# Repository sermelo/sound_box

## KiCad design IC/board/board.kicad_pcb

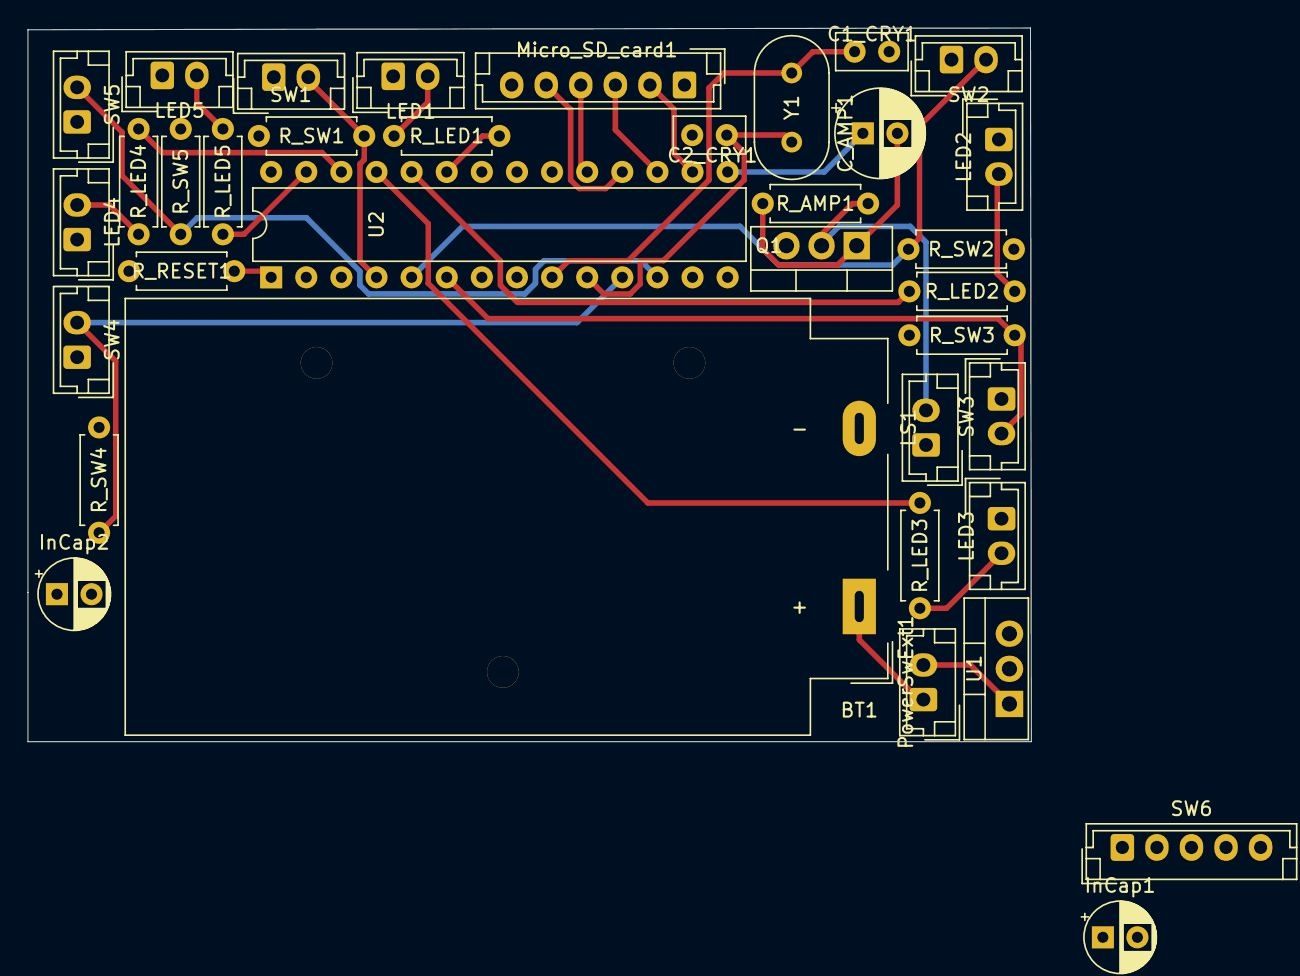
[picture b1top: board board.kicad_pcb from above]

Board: 4 copper layers, 72.6 x 51.6 mm, 36 parts (0 on the bottom side), 28 nets.

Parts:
BT1: 9V; BatteryHolder_MPD_BA9VPC_1xPP3
C1_CRY1, C2_CRY1: 22pF; C_Disc_D5.0mm_W2.5mm_P2.50mm
C_AMP1: 100uF; CP_Radial_D6.3mm_P2.50mm
InCap1: 0.33uF; CP_Radial_D5.0mm_P2.50mm
InCap2: 0.1uF; CP_Radial_D5.0mm_P2.50mm
LED1, LED2, LED3, LED4, LED5: LED; JST_EH_B2B-EH-A_1x02_P2.50mm_Vertical
LS1: Speaker; JST_EH_B2B-EH-A_1x02_P2.50mm_Vertical
Micro_SD_card1: Conn_01x06_Female; JST_EH_B6B-EH-A_1x06_P2.50mm_Vertical
PowerSwExt1: SW_DPST_x2; JST_EH_B2B-EH-A_1x02_P2.50mm_Vertical
Q1: IRLZ44N; TO-220-3_Vertical
R_AMP1: 10K; R_Axial_DIN0207_L6.3mm_D2.5mm_P7.62mm_Horizontal
R_LED1, R_LED2, R_LED3, R_LED4, R_LED5: 290; R_Axial_DIN0207_L6.3mm_D2.5mm_P7.62mm_Horizontal
R_RESET1: 10K; R_Axial_DIN0207_L6.3mm_D2.5mm_P7.62mm_Horizontal
R_SW1, R_SW2, R_SW3, R_SW4, R_SW5: 10K; R_Axial_DIN0207_L6.3mm_D2.5mm_P7.62mm_Horizontal
SW1, SW2, SW3, SW4, SW5: SW_Push; JST_EH_B2B-EH-A_1x02_P2.50mm_Vertical
SW6: Rotary_Encoder_Switch; JST_EH_B5B-EH-A_1x05_P2.50mm_Vertical
U1: L7805; TO-220-3_Vertical
U2: ATmega328P-PU; DIP-28_W7.62mm
Y1: 16Mhz; Resonator-2Pin_W10.0mm_H5.0mm

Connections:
unnamed: BT1.1, InCap1.1, PowerSwExt1.1
unnamed: BT1.2, C1_CRY1.2, C2_CRY1.2, InCap1.2, InCap2.2, LED1.1, LED2.1, LED3.1, LED4.1, LED5.1, Micro_SD_card1.6, Q1.3, SW1.1, SW2.1, SW3.1, SW4.1, SW5.1, U1.2, U2.8, U2.22
unnamed: C1_CRY1.1, U2.9, Y1.1
unnamed: C2_CRY1.1, U2.10, Y1.2
unnamed: C_AMP1.1, U2.15
unnamed: C_AMP1.2, Q1.1, R_AMP1.1
unnamed: InCap2.1, LS1.1, Micro_SD_card1.1, R_RESET1.2, R_SW1.1, R_SW2.1, R_SW3.1, R_SW4.1, R_SW5.1, U1.3, U2.7, U2.20
unnamed: LED1.2, R_LED1.1
unnamed: LED2.2, R_LED2.1
unnamed: LED3.2, R_LED3.1
unnamed: LED4.2, R_LED4.1
unnamed: LED5.2, R_LED5.1
unnamed: LS1.2, Q1.2, R_AMP1.2
unnamed: Micro_SD_card1.2, U2.16
unnamed: Micro_SD_card1.3, U2.17
unnamed: Micro_SD_card1.4, U2.19
unnamed: Micro_SD_card1.5, U2.18
unnamed: R_LED1.2, U2.23
unnamed: R_LED2.2, U2.24
unnamed: R_LED3.2, U2.25
unnamed: R_LED4.2, U2.26
unnamed: R_LED5.2, U2.27
unnamed: R_RESET1.1, U2.1
unnamed: R_SW1.2, SW1.2, U2.4
unnamed: R_SW2.2, SW2.2, U2.5
unnamed: R_SW3.2, SW3.2, U2.6
unnamed: R_SW4.2, SW4.2, U2.11
unnamed: R_SW5.2, SW5.2, U2.12

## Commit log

2022-03-02 Add current version
2022-03-07 Update the Cad and and new code
2022-03-11 Add gitignore file
2022-03-11 Clean cad files
2022-03-11 Add IC designs
2022-06-08 Update to las kicad version
2022-06-08 Add PAM amplifier
2022-06-08 Remove LED resistors. With new buttons they are not needed
2022-06-08 Add self power off circuit
2022-06-09 Add consumption data
2022-06-10 Use rotary encoder
2022-06-14 Add diode to control button
2022-06-14 Add self power off arduino code
2022-06-17 Improve self power arduino code
